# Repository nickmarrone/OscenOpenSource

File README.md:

# Oscen Open Source

Open source hardware designs for **Oscen Eurorack Modules**.

This repository contains the KiCad design files (schematics, PCB layouts, panels)
and manufacturing outputs (Gerbers, BOMs, pick-and-place files) for a selection of
Oscen's Eurorack modules, released for the community to study, build, and remix.

## Modules

| Module | Format | Description |
| --- | --- | --- |
| [Quad Passive Switch](QuadPassiveSwitch/) | 4HP, 3U | Four independent SPDT passive switches for manually routing signals — no power required. |

### Quad Passive Switch

A 4HP utility module with four independent **SPDT (single-pole, double-throw)**
toggle switches. Each section takes one input and routes it to one of two outputs
(or, run in reverse, selects between two inputs feeding a single output). The
signal path is entirely passive, so the module needs no power and adds no coloration
— useful for routing audio, CV, gates, clocks, or triggers.

See the [module README](QuadPassiveSwitch/README.md) for full details.

## Repository layout

Each module lives in its own directory and contains:

- `*.kicad_sch` — schematic
- `*.kicad_pcb` — main PCB layout
- `*_faceplate.kicad_pcb` — panel / faceplate layout
- `*.kicad_pro` / `*.kicad_prl` — KiCad project files
- `*.pdf` — rendered schematic
- `production/` — Gerbers, drill files, BOM, and pick-and-place outputs ready for fabrication

## Building these modules

1. Open the module's `.kicad_pro` in [KiCad](https://www.kicad.org/) (8.0 or newer) to view or edit the design.
2. To fabricate, send the Gerber `.zip` files in the module's `production/` directory
   to a PCB manufacturer, along with the BOM (`*_bom.csv`) and position
   (`*_positions.csv`) files if you want assembly.

## License

These designs are released as open source hardware. Unless otherwise noted in a
module's directory, you are free to build, modify, and share them. Please credit
**Oscen Modules**.

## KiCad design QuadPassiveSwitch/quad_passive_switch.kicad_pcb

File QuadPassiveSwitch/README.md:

# Quad Passive Switch

A 4HP, 3U Eurorack utility module with four independent **SPDT** (single-pole,
double-throw) passive switches. Each section manually routes one signal between two
destinations using a sub-mini toggle switch. The whole module is passive — it needs
**no power** and adds no buffering or coloration to the signal.

## Specifications

| | |
| --- | --- |
| Format | Eurorack, 3U |
| Width | 4HP (20 mm) |
| Panel height | 128.5 mm |
| Depth | Shallow (passive, no power header) |
| Power | None required |
| Switches | 4 × SPDT sub-mini toggle |
| Jacks | 12 × 3.5 mm mono switched |

## How it works

The module is divided into four identical sections, arranged top-left (TL),
top-right (TR), bottom-left (BL), and bottom-right (BR). Each section has:

- **IN** — signal input
- **OUT 1** — output selected when the toggle is in position 1
- **OUT 2** — output selected when the toggle is in position 2

The toggle switch connects **IN** to either **OUT 1** or **OUT 2**. Because the
path is just a mechanical contact, it works with any signal: audio, CV, gates,
clocks, or triggers.

### Reverse use (2-to-1)

Since the switch is passive and symmetrical, each section can be used in reverse:
patch two sources into **OUT 1** and **OUT 2**, and the toggle selects which one
appears at **IN**. In this mode **IN** becomes the output and the OUTs become inputs.

> Note: as with any passive multiple/switch, only patch a signal into one side of a
> given section at a time when using it in reverse, to avoid summing or back-feeding
> sources.

## Bill of materials

| Designators | Qty | Part | Footprint |
| --- | --- | --- | --- |
| J1–J12 | 12 | 3.5 mm mono switched jack (PJ398SM) | `EighthInch_PJ398SM` |
| SW1–SW4 | 4 | SPDT sub-mini toggle | `Switch_Toggle_SPDT_SubMini` |

See [`production/quad_passive_switch_gerbers_v1.0_bom.csv`](production/quad_passive_switch_gerbers_v1.0_bom.csv)
for the fabrication BOM.

## Files

- `quad_passive_switch.kicad_sch` — schematic
- `quad_passive_switch.kicad_pcb` — main PCB layout
- `quad_passive_switch_faceplate.kicad_pcb` — panel / faceplate layout
- `quad_passive_switch.pdf` — rendered schematic
- `quad_passive_switch.kicad_pro` — KiCad project
- `production/` — Gerbers (`*_gerbers_v1.0.zip`, `*_faceplate_gerbers_v1.0.zip`),
  drill/netlist, BOM, designators, and pick-and-place position files for v1.0

## Building it

1. Open `quad_passive_switch.kicad_pro` in [KiCad](https://www.kicad.org/) 8.0+ to
   inspect or modify the design.
2. To fabricate, send `production/quad_passive_switch_gerbers_v1.0.zip` (PCB) and
   `production/quad_passive_switch_faceplate_gerbers_v1.0.zip` (panel) to a PCB
   manufacturer.
3. Solder the 12 jacks and 4 toggle switches per the BOM. There are no other
   components — no resistors, ICs, or power connector.

## Revision

- **v1.0** — initial release.

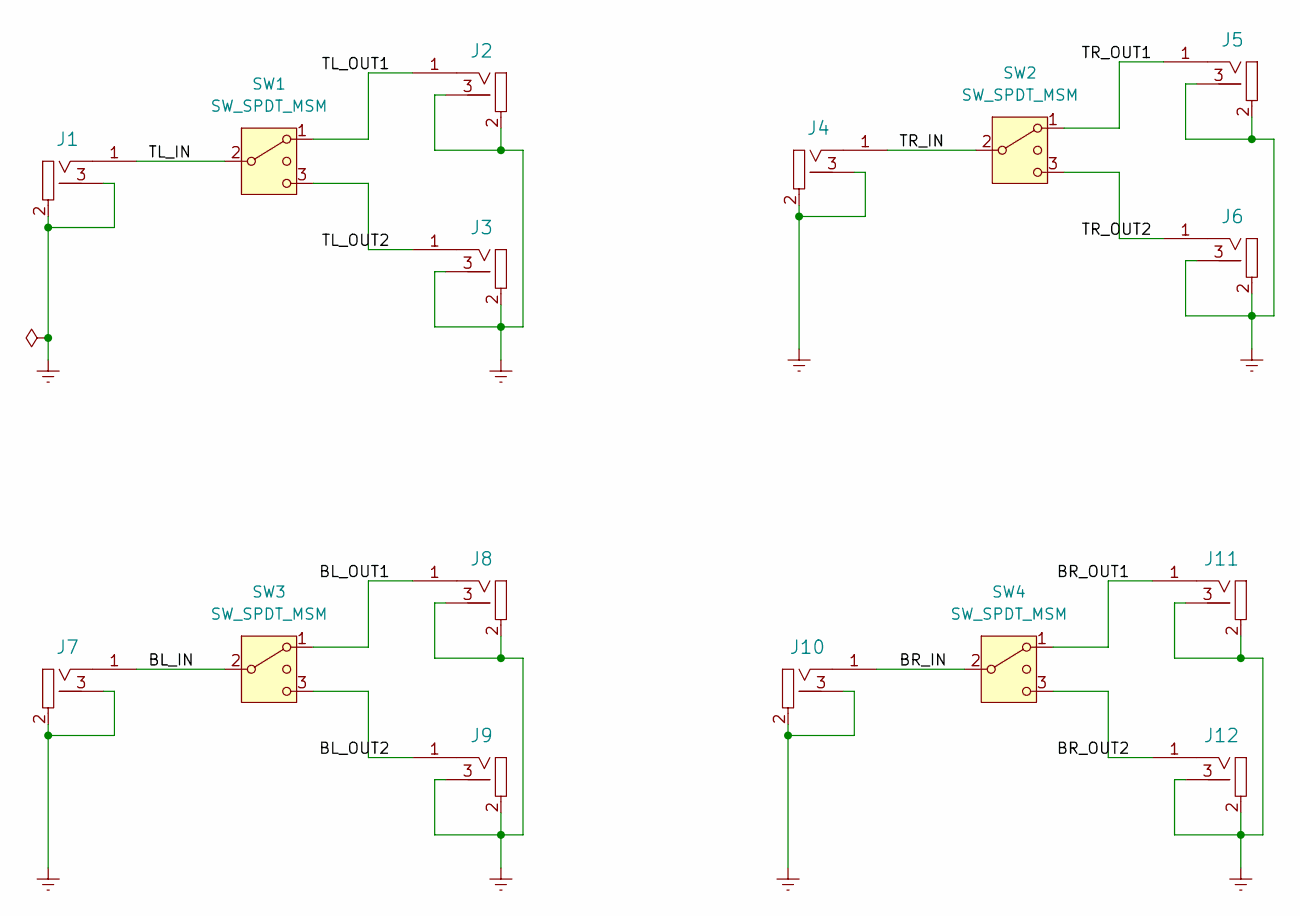
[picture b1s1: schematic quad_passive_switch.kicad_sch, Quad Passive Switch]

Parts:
J1, J2, J3, J4, J5, J6, J7, J8, J9, J10, J11, J12: 3.5mm_Mono_Switched_SymSmall_0.05; EighthInch_PJ398SM; Part Number WQP-WQP518MA
SW1, SW2, SW3, SW4: SW_SPDT_MSM; Switch_Toggle_SPDT_SubMini

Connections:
/BL_IN: J7.1 (SIG), SW3.2 (3)
/BL_OUT1: J8.1 (SIG), SW3.1
/BL_OUT2: J9.1 (SIG), SW3.3 (4)
/BR_IN: J10.1 (SIG), SW4.2 (3)
/BR_OUT1: J11.1 (SIG), SW4.1
/BR_OUT2: J12.1 (SIG), SW4.3 (4)
/TL_IN: J1.1 (SIG), SW1.2 (3)
/TL_OUT1: J2.1 (SIG), SW1.1
/TL_OUT2: J3.1 (SIG), SW1.3 (4)
/TR_IN: J4.1 (SIG), SW2.2 (3)
/TR_OUT1: J5.1 (SIG), SW2.1
/TR_OUT2: J6.1 (SIG), SW2.3 (4)
GNDREF: J1.2 (SHEILD), J1.3 (SW), J2.2 (SHEILD), J2.3 (SW), J3.2 (SHEILD), J3.3 (SW), J4.2 (SHEILD), J4.3 (SW), J5.2 (SHEILD), J5.3 (SW), J6.2 (SHEILD), J6.3 (SW), J7.2 (SHEILD), J7.3 (SW), J8.2 (SHEILD), J8.3 (SW), J9.2 (SHEILD), J9.3 (SW), J10.2 (SHEILD), J10.3 (SW), J11.2 (SHEILD), J11.3 (SW), J12.2 (SHEILD), J12.3 (SW)

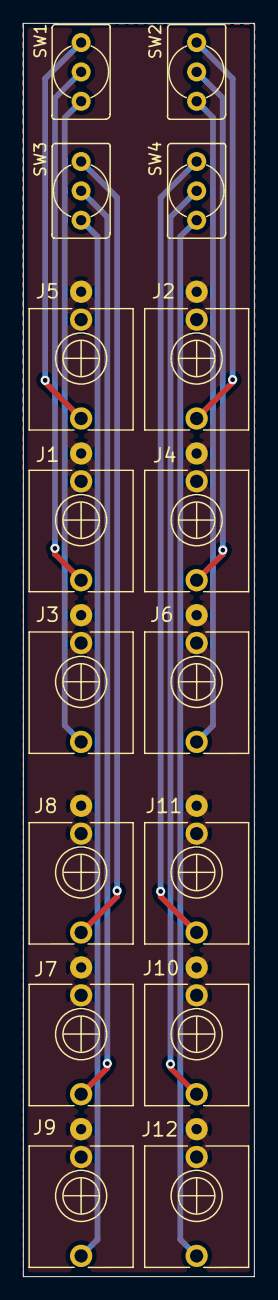
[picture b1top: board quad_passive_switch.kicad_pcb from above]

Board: 2 copper layers, 20.0 x 108.5 mm, 16 parts (0 on the bottom side), 13 nets.

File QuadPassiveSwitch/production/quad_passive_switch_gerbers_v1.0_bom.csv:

Designator,Footprint,Quantity,Value,LCSC Part #
"J1, J10, J11, J12, J2, J3, J4, J5, J6, J7, J8, J9",EighthInch_PJ398SM,12,3.5mm_Mono_Switched_SymSmall_0.05,
"SW1, SW2, SW3, SW4",Switch_Toggle_SPDT_SubMini,4,SW_SPDT_MSM,

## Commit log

2026-06-09 Quad Passive Switch
    Add quad passive switch module. This takes four signals and allows the user to manually switch between two outs (or two ins) during a performance.
2026-06-09 Add GNU GPL v3 license text
    This commit adds the full text of the GNU General Public License version 3 to the LICENSE file.
2026-06-09 Add README.md
2026-06-09 Add iBOM for quad passive switch
2026-06-09 Add version to quad passive switch PCB
